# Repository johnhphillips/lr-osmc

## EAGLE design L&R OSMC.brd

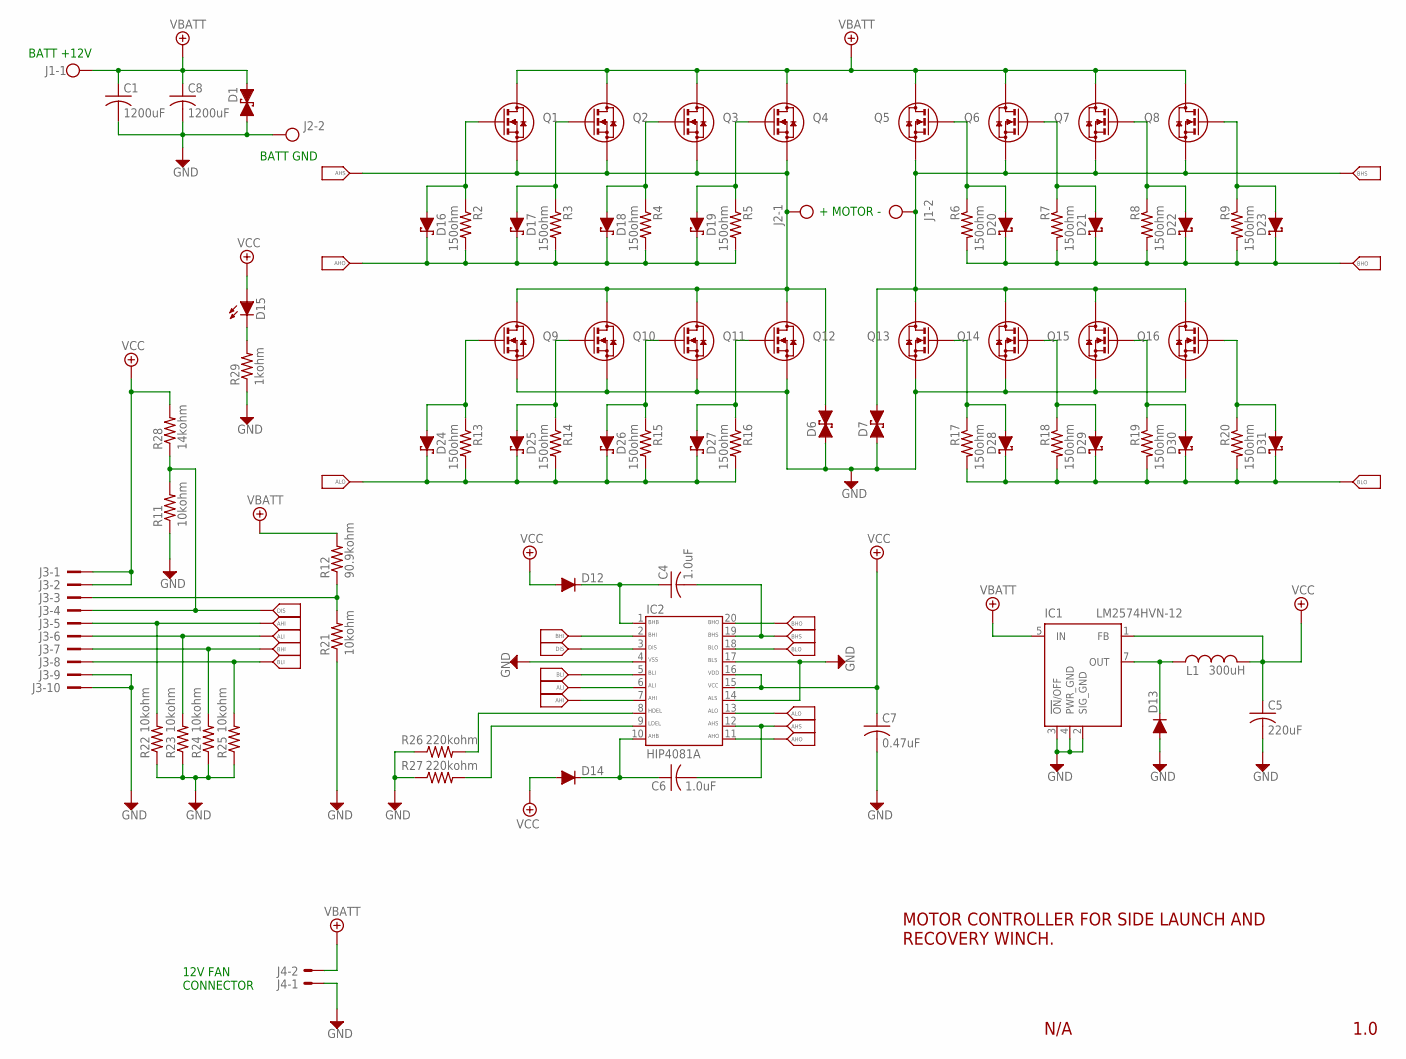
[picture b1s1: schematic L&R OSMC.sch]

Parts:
C1, C8: 1200uF; E7,5-18
C4, C6: 1.0uF; C050-075X075
C5: 220uF; E5-6
C7: 0.47uF; C050-025X075
D1, D6, D7: 1.5KE51CA; 1.5KE
D12, D13, D14: UF1002; DO41
D15: LED; LED5MM
D16, D17, D18, D19, D20, D21, D22, D23, D24, D25, D26, D27, D28, D29, D30, D31: 1N6263; DO35-7
IC1: LM2574HVN-12; DIL08
IC2: HIP4081A; DIL20
J1, J2: LXXX-2
J3: 3793; 3M/3793-10
J4: 22-23-2021
L1: 300uH; L06X18
Q1, Q2, Q3, Q4, Q5, Q6, Q7, Q8, Q9, Q10, Q11, Q12, Q13, Q14, Q15, Q16: IRF14051-16; TO-220AB
R2, R3, R4, R5, R6, R7, R8, R9, R13, R14, R15, R16, R17, R18, R19, R20: 150ohm; 0207/7
R11, R21, R22, R23, R24, R25: 10kohm; 0207/7
R12: 90.9kohm; 0207/7
R26, R27: 220kohm; 0207/7
R28: 14kohm; 0207/7
R29: 1kohm; 0207/7

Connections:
+12V: C5.+ (1), C7.1, D12.A, D14.A, D15.A, IC1.1 (FB), IC2.15, IC2.16, J3.P$1, J3.P$2, L1.2, R28.2
AHI: IC2.7, J3.P$5, R22.2
AHO: D16.C, D17.C, D18.C, D19.C, IC2.11, R2.2, R3.2, R4.2, R5.2
AHS: C6.2, D6.C (2), IC2.12, J2.P$1, J2.P$2, J2.P$3, J2.P$4, Q1.D, Q2.D, Q3.D, Q4.D, Q9.S, Q10.S, Q11.S, Q12.S
ALI: IC2.6, J3.P$6, R23.2
ALO: D24.C, D25.C, D26.C, D27.C, IC2.13, R13.2, R14.2, R15.2, R16.2
BHI: IC2.2, J3.P$7, R24.2
BHO: D20.C, D21.C, D22.C, D23.C, IC2.20, R6.2, R7.2, R8.2, R9.2
BHS: C4.2, D7.C (2), IC2.19, J1.P$5, J1.P$6, J1.P$7, J1.P$8, Q5.D, Q6.D, Q7.D, Q8.D, Q13.S, Q14.S, Q15.S, Q16.S
BLI: IC2.5, J3.P$8, R25.2
BLO: D28.C, D29.C, D30.C, D31.C, IC2.18, R17.2, R18.2, R19.2, R20.2
DIS: IC2.3, J3.P$4, R11.2, R28.1
GND: C1.- (2), C5.- (2), C7.2, C8.- (2), D1.A (1), D6.A (1), D7.A (1), D13.A, IC1.2 (SIG_GND), IC1.3 (!ON!/OFF), IC1.4 (PWR_GND), IC2.4, IC2.14, IC2.17, J2.P$5, J2.P$6, J2.P$7, J2.P$8, J3.P$9, J3.P$10, J4.1, Q9.D, Q10.D, Q11.D, Q12.D, Q13.D, Q14.D, Q15.D, Q16.D, R11.1, R21.1, R22.1, R23.1, R24.1, R25.1, R26.1, R27.1, R29.1
unnamed: D13.C, IC1.7 (OUT), L1.1
unnamed: C4.1, D12.C, IC2.1
unnamed: D16.A, Q1.G, R2.1
unnamed: D23.A, Q8.G, R9.1
unnamed: D17.A, Q2.G, R3.1
unnamed: D18.A, Q3.G, R4.1
unnamed: D19.A, Q4.G, R5.1
unnamed: D22.A, Q7.G, R8.1
unnamed: D21.A, Q6.G, R7.1
unnamed: D20.A, Q5.G, R6.1
unnamed: IC2.9, R27.2
unnamed: D24.A, Q9.G, R13.1
unnamed: D25.A, Q10.G, R14.1
unnamed: D26.A, Q11.G, R15.1
unnamed: D27.A, Q12.G, R16.1
unnamed: IC2.8, R26.2
unnamed: D31.A, Q16.G, R20.1
unnamed: D30.A, Q15.G, R19.1
unnamed: D29.A, Q14.G, R18.1
unnamed: D28.A, Q13.G, R17.1
unnamed: D15.K (C), R29.2
unnamed: C6.1, D14.C, IC2.10
unnamed: J3.P$3, R12.1, R21.2
VBATT: C1.+ (1), C8.+ (1), D1.C (2), IC1.5 (IN), J1.P$1, J1.P$2, J1.P$3, J1.P$4, J4.2, Q1.S, Q2.S, Q3.S, Q4.S, Q5.S, Q6.S, Q7.S, Q8.S, R12.2

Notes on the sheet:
BATT +12V
BATT GND
N/A
1.0
MOTOR CONTROLLER FOR SIDE LAUNCH AND RECOVERY WINCH.
12V FAN CONNECTOR
+ MOTOR -

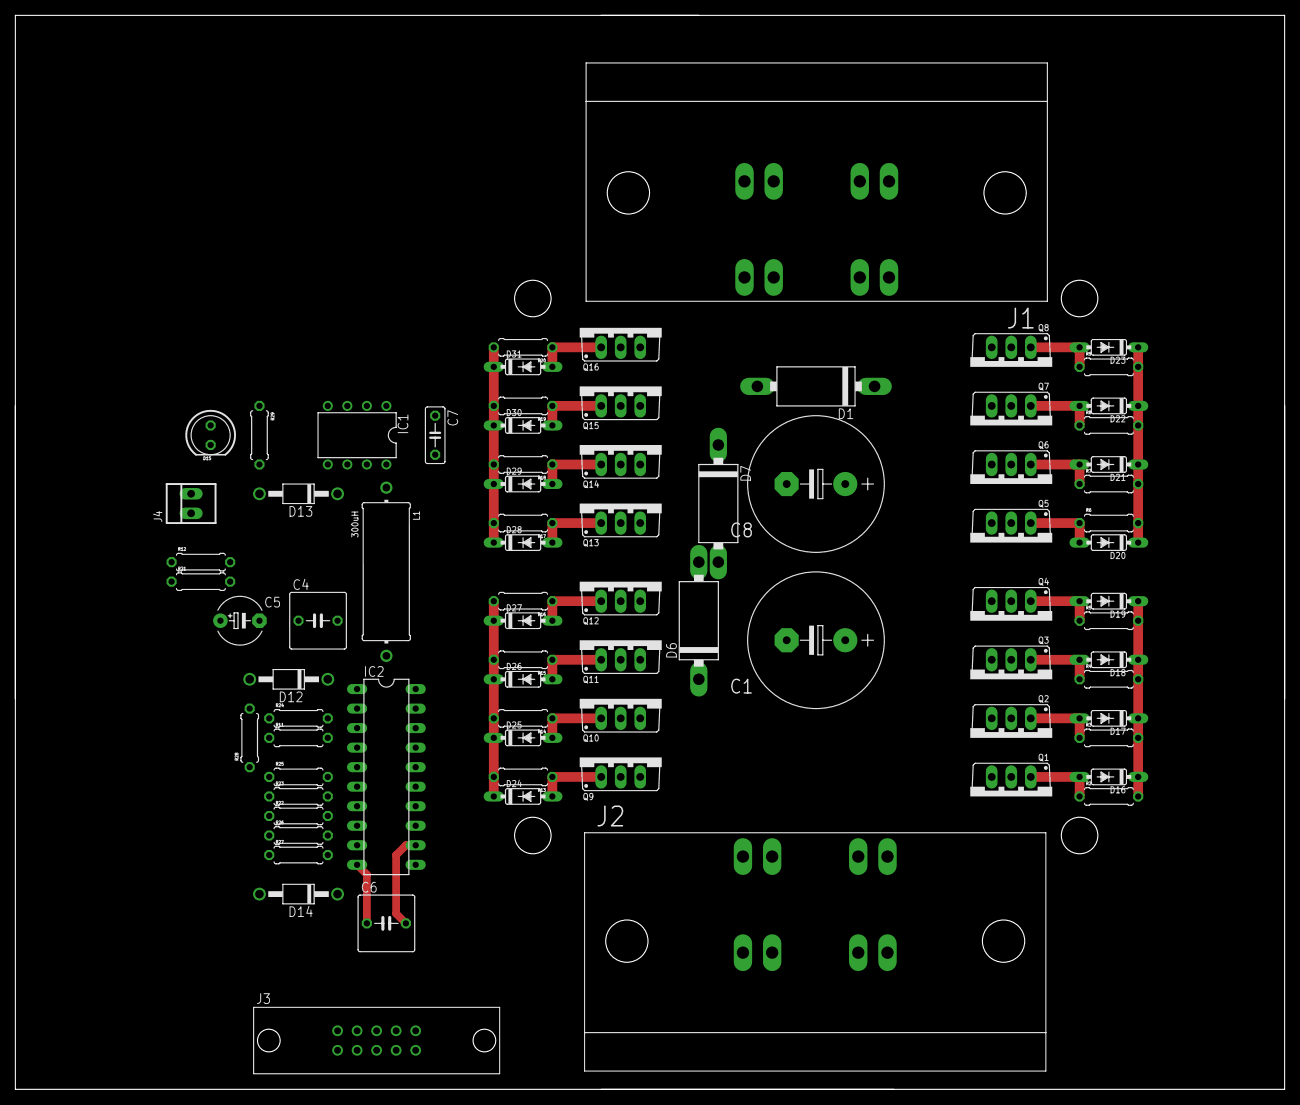
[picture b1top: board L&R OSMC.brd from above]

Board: 2 copper layers, 165.1 x 139.7 mm, 79 parts (0 on the bottom side), 37 nets.

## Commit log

2013-09-04 Added .gitignore and .gitattributes
2014-03-27 Added eagle.epf file
